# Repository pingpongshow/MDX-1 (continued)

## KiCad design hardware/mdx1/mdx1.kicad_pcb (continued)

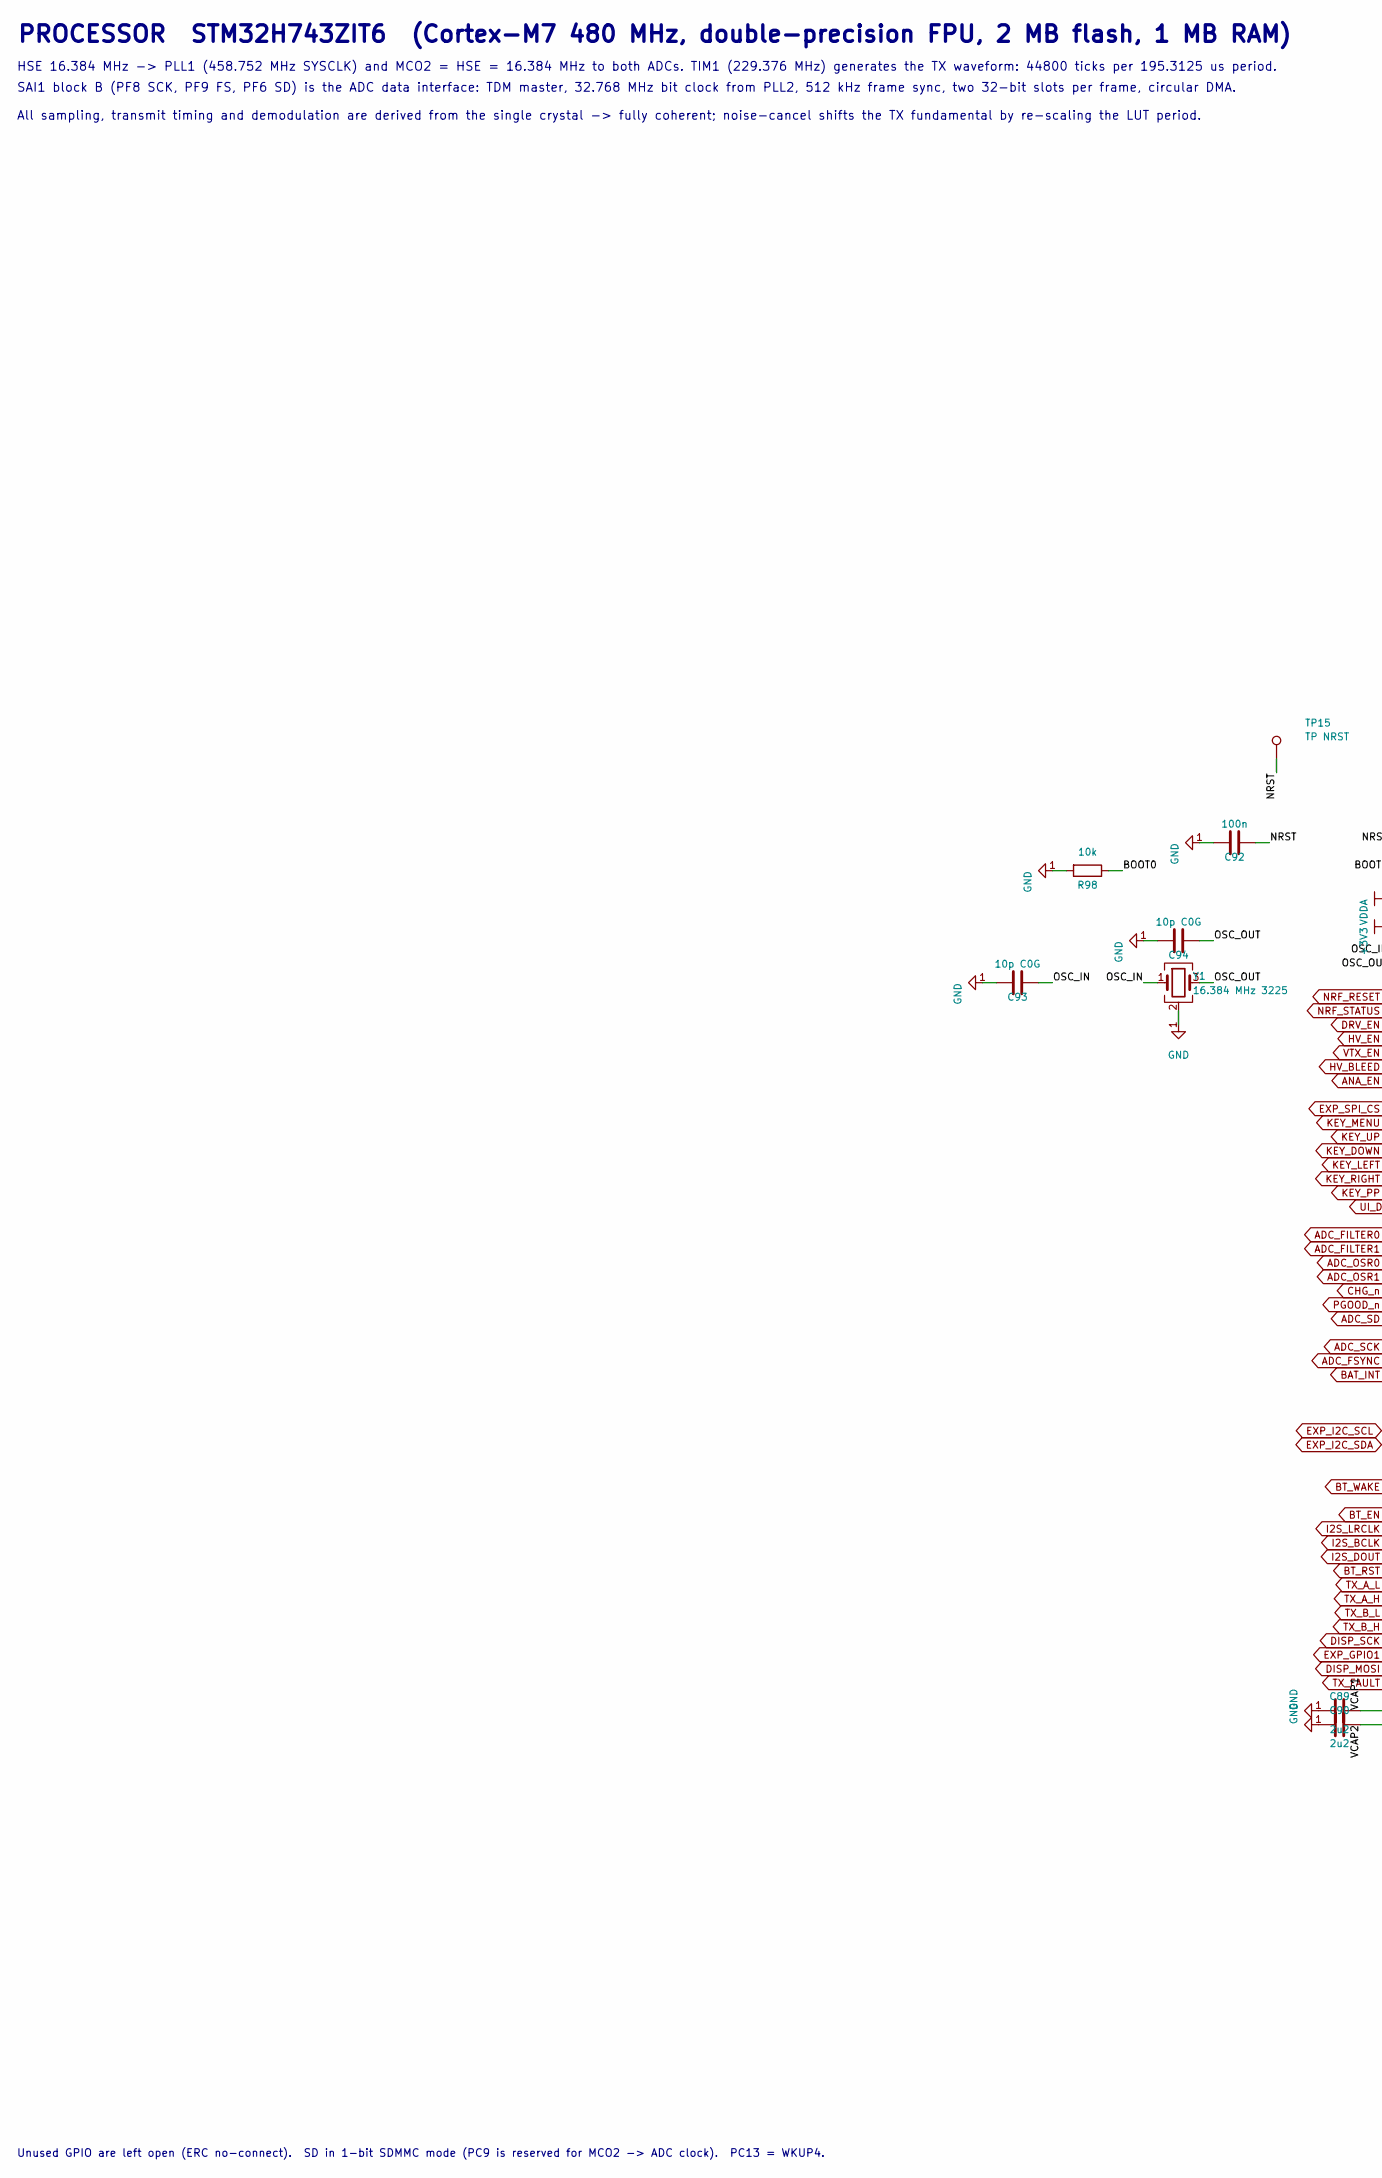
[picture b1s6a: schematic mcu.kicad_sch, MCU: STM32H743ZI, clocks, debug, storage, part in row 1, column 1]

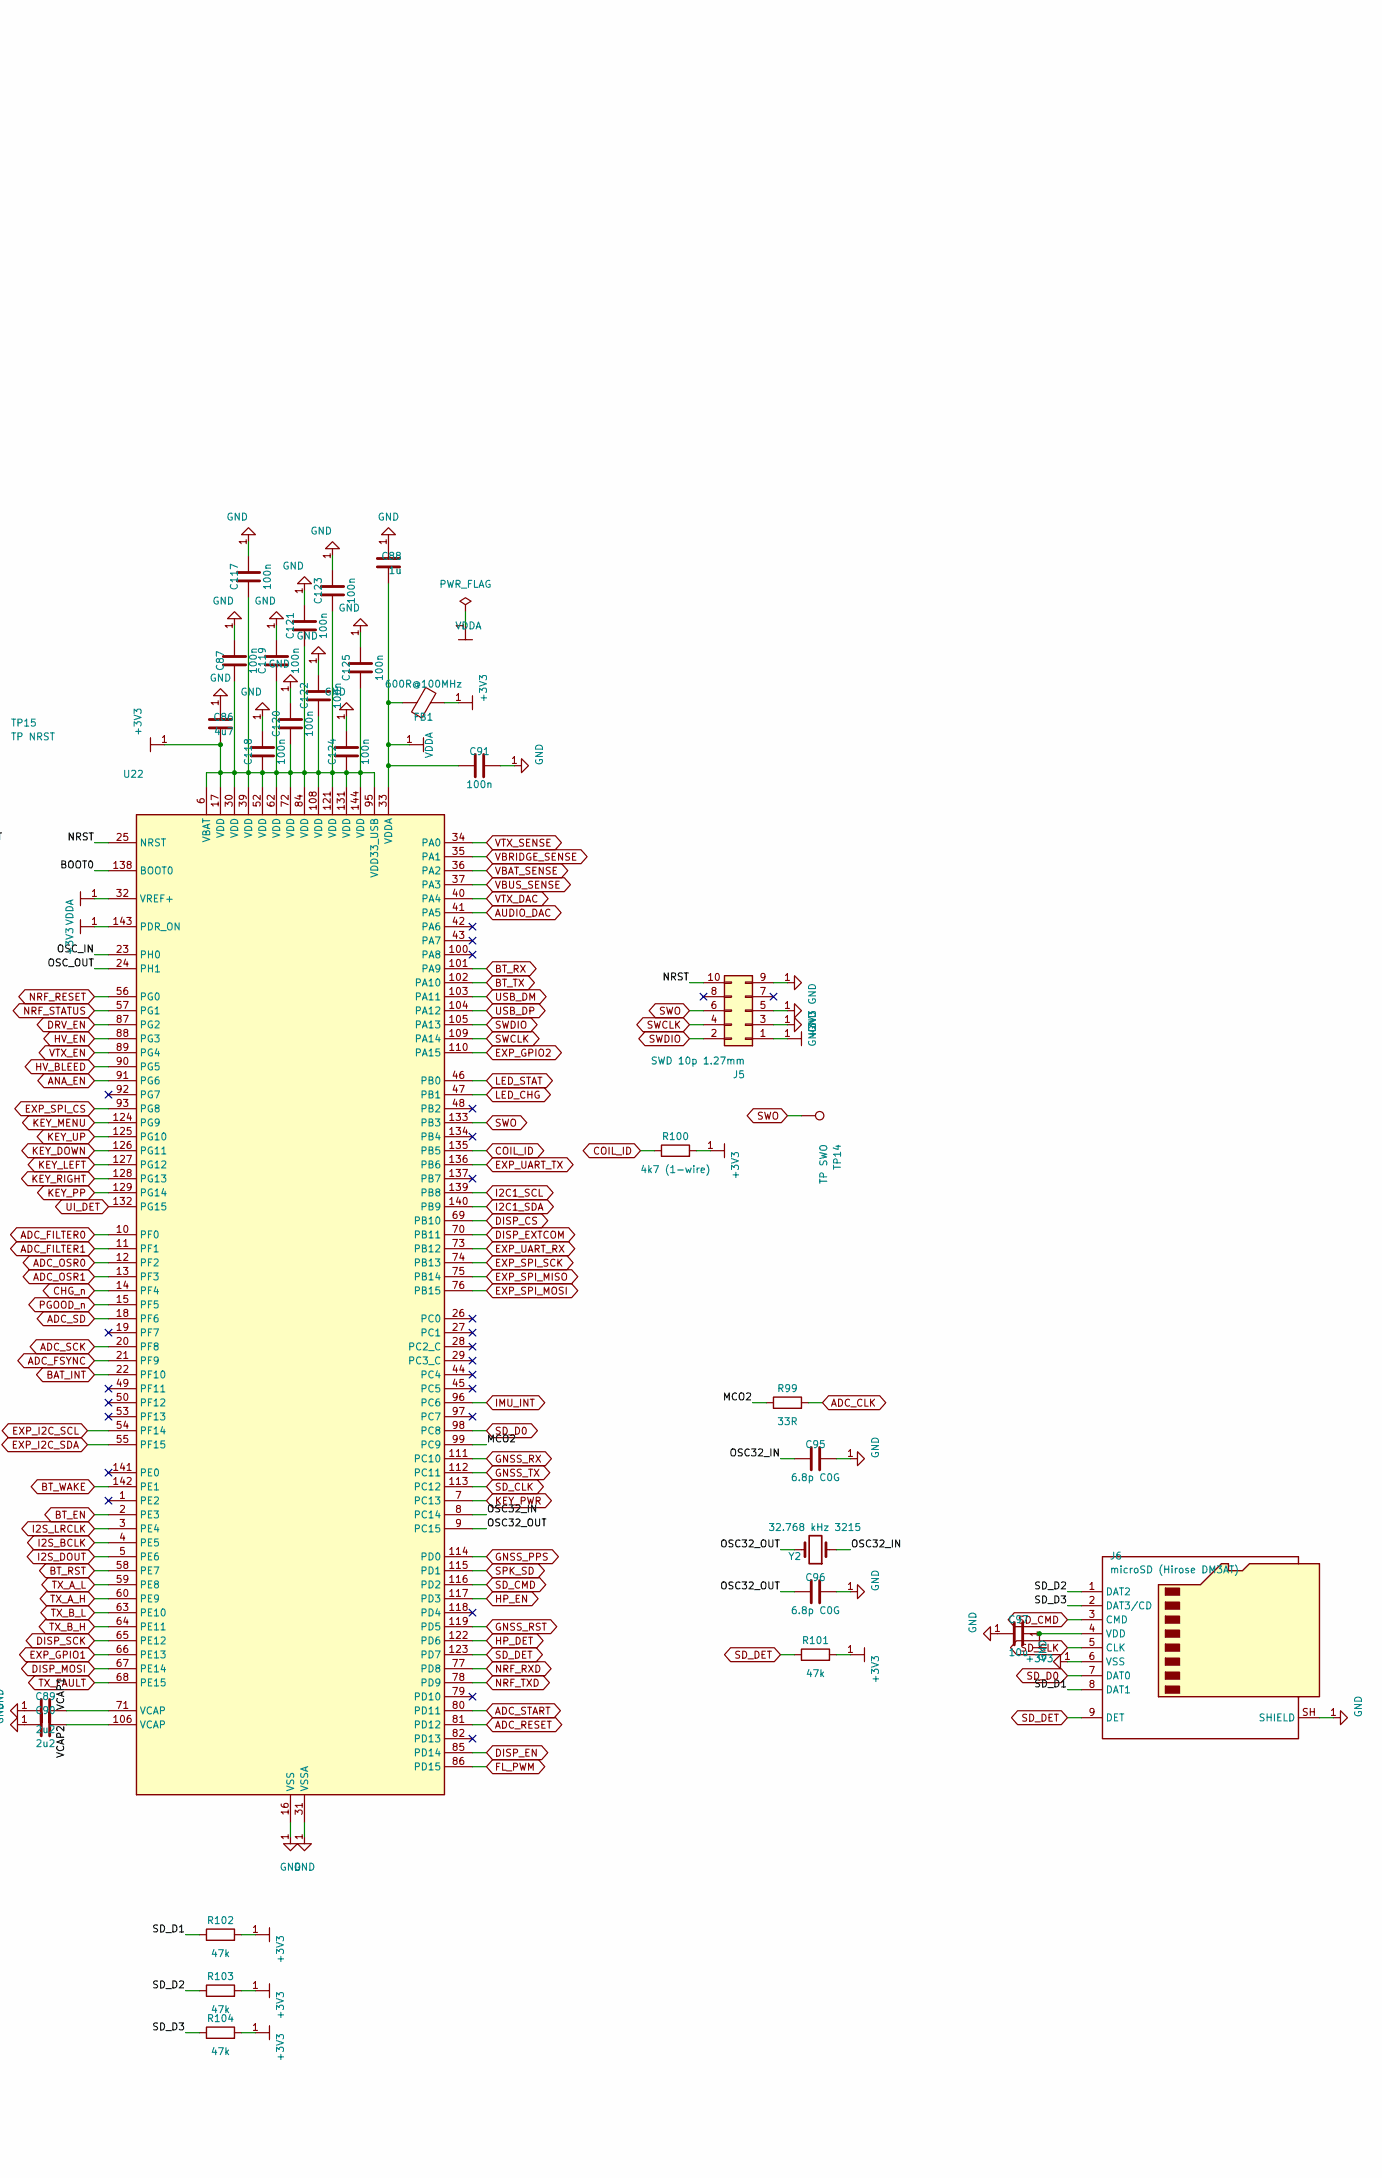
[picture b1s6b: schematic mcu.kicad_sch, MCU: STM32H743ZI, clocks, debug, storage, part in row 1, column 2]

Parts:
C86: 4u7; C_0603_1608Metric
C87, C91, C92, C117, C118, C119, C120, C121, C122, C123, C124, C125: 100n; C_0402_1005Metric
C88: 1u; C_0603_1608Metric
C89, C90: 2u2; C_0603_1608Metric
C93, C94: 10p C0G; C_0402_1005Metric
C95, C96: 6.8p C0G; C_0402_1005Metric
C97: 10u; C_0805_2012Metric
FB1: 600R@100MHz; L_0603_1608Metric
J5: SWD 10p 1.27mm; PinHeader_2x05_P1.27mm_Vertical
J6: microSD (Hirose DM3AT); microSD_HC_Hirose_DM3AT-SF-PEJM5
R98: 10k; R_0402_1005Metric
R99: 33R; R_0402_1005Metric
R100: 4k7 (1-wire); R_0402_1005Metric
R101, R102, R103, R104: 47k; R_0402_1005Metric
TP14: TP SWO; TestPoint_Pad_D1.5mm
TP15: TP NRST; TestPoint_Pad_D1.5mm
U22: STM32H743ZIT6; LQFP-144_20x20mm_P0.5mm
Y1: 16.384 MHz 3225; Crystal_SMD_3225-4Pin_3.2x2.5mm
Y2: 32.768 kHz 3215; Crystal_SMD_3215-2Pin_3.2x1.5mm

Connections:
+3V3: C86.1, C87.1, C97.1, C117.1, C118.1, C119.1, C120.1, C121.1, C122.1, C123.1, C124.1, C125.1, FB1.1, J5.1, J6.4 (VDD), R100.2, R101.2, R102.2, R103.2, R104.2, U22.6 (VBAT), U22.17 (VDD), U22.30 (VDD), U22.39 (VDD), U22.52 (VDD), U22.62 (VDD), U22.72 (VDD), U22.84 (VDD), U22.95 (VDD33_USB), U22.108 (VDD), U22.121 (VDD), U22.131 (VDD), U22.143 (PDR_ON), U22.144 (VDD); also elsewhere on the board
/MCU: STM32H743ZI, clocks, debug, storage/BOOT0: R98.1, U22.138 (BOOT0)
/MCU: STM32H743ZI, clocks, debug, storage/MCO2: R99.1, U22.99 (PC9)
/MCU: STM32H743ZI, clocks, debug, storage/NRST: C92.1, J5.10, TP15.1 (1_1), U22.25 (NRST)
/MCU: STM32H743ZI, clocks, debug, storage/OSC32_IN: C95.1, U22.8 (PC14), Y2.1
/MCU: STM32H743ZI, clocks, debug, storage/OSC32_OUT: C96.1, U22.9 (PC15), Y2.2
/MCU: STM32H743ZI, clocks, debug, storage/OSC_IN: C93.1, U22.23 (PH0), Y1.1
/MCU: STM32H743ZI, clocks, debug, storage/OSC_OUT: C94.1, U22.24 (PH1), Y1.3
/MCU: STM32H743ZI, clocks, debug, storage/SD_D1: J6.8 (DAT1), R102.1
/MCU: STM32H743ZI, clocks, debug, storage/SD_D2: J6.1 (DAT2), R103.1
/MCU: STM32H743ZI, clocks, debug, storage/SD_D3: J6.2 (DAT3/CD), R104.1
/MCU: STM32H743ZI, clocks, debug, storage/VCAP1: C89.1, U22.71 (VCAP)
/MCU: STM32H743ZI, clocks, debug, storage/VCAP2: C90.1, U22.106 (VCAP)
ADC_CLK: R99.2; also elsewhere on the board
ADC_FILTER0: U22.10 (PF0); also elsewhere on the board
ADC_FILTER1: U22.11 (PF1); also elsewhere on the board
ADC_FSYNC: U22.21 (PF9); also elsewhere on the board
ADC_OSR0: U22.12 (PF2); also elsewhere on the board
ADC_OSR1: U22.13 (PF3); also elsewhere on the board
ADC_RESET: U22.81 (PD12); also elsewhere on the board
ADC_SCK: U22.20 (PF8); also elsewhere on the board
ADC_SD: U22.18 (PF6); also elsewhere on the board
ADC_START: U22.80 (PD11); also elsewhere on the board
ANA_EN: U22.91 (PG6); also elsewhere on the board
AUDIO_DAC: U22.41 (PA5); also elsewhere on the board
BAT_INT: U22.22 (PF10); also elsewhere on the board
BT_EN: U22.2 (PE3); also elsewhere on the board
BT_RST: U22.58 (PE7); also elsewhere on the board
BT_RX: U22.101 (PA9); also elsewhere on the board
BT_TX: U22.102 (PA10); also elsewhere on the board
BT_WAKE: U22.142 (PE1); also elsewhere on the board
CHG_n: U22.14 (PF4); also elsewhere on the board
COIL_ID: R100.1, U22.135 (PB5); also elsewhere on the board
DISP_CS: U22.69 (PB10); also elsewhere on the board
DISP_EN: U22.85 (PD14); also elsewhere on the board
DISP_EXTCOM: U22.70 (PB11); also elsewhere on the board
DISP_MOSI: U22.67 (PE14); also elsewhere on the board
DISP_SCK: U22.65 (PE12); also elsewhere on the board
DRV_EN: U22.87 (PG2); also elsewhere on the board
EXP_GPIO1: U22.66 (PE13); also elsewhere on the board
EXP_GPIO2: U22.110 (PA15); also elsewhere on the board
EXP_I2C_SCL: U22.54 (PF14); also elsewhere on the board
EXP_I2C_SDA: U22.55 (PF15); also elsewhere on the board
EXP_SPI_CS: U22.93 (PG8); also elsewhere on the board
EXP_SPI_MISO: U22.75 (PB14); also elsewhere on the board
EXP_SPI_MOSI: U22.76 (PB15); also elsewhere on the board
EXP_SPI_SCK: U22.74 (PB13); also elsewhere on the board
EXP_UART_RX: U22.73 (PB12); also elsewhere on the board
EXP_UART_TX: U22.136 (PB6); also elsewhere on the board
FL_PWM: U22.86 (PD15); also elsewhere on the board
GNSS_PPS: U22.114 (PD0); also elsewhere on the board
GNSS_RST: U22.119 (PD5); also elsewhere on the board
GNSS_RX: U22.111 (PC10); also elsewhere on the board
GNSS_TX: U22.112 (PC11); also elsewhere on the board
HP_DET: U22.122 (PD6); also elsewhere on the board
HP_EN: U22.117 (PD3); also elsewhere on the board
HV_BLEED: U22.90 (PG5); also elsewhere on the board
HV_EN: U22.88 (PG3); also elsewhere on the board
I2C1_SCL: U22.139 (PB8); also elsewhere on the board
I2C1_SDA: U22.140 (PB9); also elsewhere on the board
I2S_BCLK: U22.4 (PE5); also elsewhere on the board
I2S_DOUT: U22.5 (PE6); also elsewhere on the board
I2S_LRCLK: U22.3 (PE4); also elsewhere on the board
IMU_INT: U22.96 (PC6); also elsewhere on the board
KEY_DOWN: U22.126 (PG11); also elsewhere on the board
KEY_LEFT: U22.127 (PG12); also elsewhere on the board
KEY_MENU: U22.124 (PG9); also elsewhere on the board
KEY_PP: U22.129 (PG14); also elsewhere on the board
KEY_PWR: U22.7 (PC13); also elsewhere on the board
KEY_RIGHT: U22.128 (PG13); also elsewhere on the board
KEY_UP: U22.125 (PG10); also elsewhere on the board
LED_CHG: U22.47 (PB1); also elsewhere on the board
LED_STAT: U22.46 (PB0); also elsewhere on the board
NRF_RESET: U22.56 (PG0); also elsewhere on the board
NRF_RXD: U22.77 (PD8); also elsewhere on the board
NRF_STATUS: U22.57 (PG1); also elsewhere on the board
NRF_TXD: U22.78 (PD9); also elsewhere on the board
PGOOD_n: U22.15 (PF5); also elsewhere on the board
SD_CLK: J6.5 (CLK), U22.113 (PC12)
SD_CMD: J6.3 (CMD), U22.116 (PD2)
SD_D0: J6.7 (DAT0), U22.98 (PC8)
SD_DET: J6.9 (DET), R101.1, U22.123 (PD7)
SPK_SD: U22.115 (PD1); also elsewhere on the board
SWCLK: J5.4, U22.109 (PA14)
SWDIO: J5.2, U22.105 (PA13)
SWO: J5.6, TP14.1 (1_1), U22.133 (PB3)
TX_A_H: U22.60 (PE9); also elsewhere on the board
TX_A_L: U22.59 (PE8); also elsewhere on the board
TX_B_H: U22.64 (PE11); also elsewhere on the board
TX_B_L: U22.63 (PE10); also elsewhere on the board
TX_FAULT: U22.68 (PE15); also elsewhere on the board
UI_DET: U22.132 (PG15); also elsewhere on the board
USB_DM: U22.103 (PA11); also elsewhere on the board
USB_DP: U22.104 (PA12); also elsewhere on the board
VBAT_SENSE: U22.36 (PA2); also elsewhere on the board
VBRIDGE_SENSE: U22.35 (PA1); also elsewhere on the board
VBUS_SENSE: U22.37 (PA3); also elsewhere on the board
VDDA: C88.1, C91.1, FB1.2, U22.32 (VREF+), U22.33 (VDDA)
VTX_DAC: U22.40 (PA4); also elsewhere on the board
VTX_EN: U22.89 (PG4); also elsewhere on the board
VTX_SENSE: U22.34 (PA0); also elsewhere on the board

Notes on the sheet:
SAI1 block B (PF8 SCK, PF9 FS, PF6 SD) is the ADC data interface: TDM master, 32.768 MHz bit clock from PLL2, 512 kHz frame sync, two 32-bit slots per frame, circular DMA.
All sampling, transmit timing and demodulation are derived from the single crystal -> fully coherent; noise-cancel shifts the TX fundamental by re-scaling the LUT period.
HSE 16.384 MHz -> PLL1 (458.752 MHz SYSCLK) and MCO2 = HSE = 16.384 MHz to both ADCs. TIM1 (229.376 MHz) generates the TX waveform: 44800 ticks per 195.3125 us period.
Unused GPIO are left open (ERC no-connect). SD in 1-bit SDMMC mode (PC9 is reserved for MCO2 -> ADC clock). PC13 = WKUP4.
PROCESSOR STM32H743ZIT6 (Cortex-M7 480 MHz, double-precision FPU, 2 MB flash, 1 MB RAM)

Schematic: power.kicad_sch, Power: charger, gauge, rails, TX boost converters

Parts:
C1, C27: 4u7 10V; C_0603_1608Metric
C2, C3, C6, C9, C26: 10u 10V; C_0805_2012Metric
C4, C10, C28: 100n; C_0402_1005Metric
C5, C24, C25: 1u; C_0603_1608Metric
C7, C8: 22u 6.3V; C_0805_2012Metric
C11, C34: 220n; C_0402_1005Metric
C12: 10n (CP); C_0402_1005Metric
C13: 4n7 (CN); C_0402_1005Metric
C14, C15, C16: 22u 25V; C_1210_3225Metric
C17: 1u 25V; C_0603_1608Metric
C18, C21: 4u7 25V; C_0805_2012Metric
C19, C22: 10u 25V; C_0805_2012Metric
C20, C23, C29, C35: 4u7; C_0603_1608Metric
C30: 4n7; C_0402_1005Metric
C31: 100u 50V; CP_Radial_D8.0mm_P3.50mm
C32: 10u 50V; C_1210_3225Metric
C33: 4u7 50V; C_1210_3225Metric
C36: 10n; C_0402_1005Metric
C37: 47u 160V; CP_Radial_D10.0mm_P5.00mm
C38, C39: 2u2 250V; C_2220_5750Metric
D1: SMAJ5.0A TVS; D_SMA
D2, D3: SS34; D_SMA
D4: B560C 60V 5A; D_SMC
D5: STPS2150 150V; D_SMA
J1: USB-C 16P; USB_C_Receptacle_HRO_TYPE-C-31-M-12
J2: USBLC6-2SC6 (USB ESD); SOT-23-6
J3: Battery JST-PH 3p; JST_PH_B3B-PH-K_1x03_P2.00mm_Vertical
L1: 1u5 XAL4020; L_Coilcraft_XAL4020-XXX
L2, L3: 4u7 XAL4020; L_Coilcraft_XAL4020-XXX
L4: 22u XAL7050; L_Coilcraft_XAL7050-XXX
L5: 47u XAL7050; L_Coilcraft_XAL7050-XXX
Q1: SiR680ADP-T1-UE3; PowerPAK_SO-8_Single
Q2: BSC190N15NS3 (150V); Infineon_PG-TDSON-8_6.15x5.15mm
Q3: BSS127S (600V); SOT-23
R1, R2: 5k1; R_0402_1005Metric
R3: 1k1 (IIN 1.4A); R_0402_1005Metric
R4: 887R (ICHG 1A); R_0402_1005Metric
R5: 47k (timer); R_0402_1005Metric
R6: 10k (TS, DNP w/ NTC); R_0402_1005Metric
R7, R8, R14, R15, R24, R46: 100k; R_0402_1005Metric
R9: 10m 1% (gauge); R_1206_3216Metric
R10, R11, R16, R19, R37: 10k; R_0402_1005Metric
R12, R13: 4k7; R_0402_1005Metric
R17, R36: 47k; R_0402_1005Metric
R18, R29, R39: 22k; R_0402_1005Metric
R20: 100R (VIN filter); R_0402_1005Metric
R21: 1M; R_0402_1005Metric
R22: 113k; R_0402_1005Metric
R23: 499k; R_0402_1005Metric
R25, R26: 49k9 0.1% SET (100uA); R_0402_1005Metric
R27: 10R (LCD supply); R_0402_1005Metric
R28: 41k2 (300kHz); R_0402_1005Metric
R30, R35: 442k; R_0402_1005Metric
R31: 40k2; R_0402_1005Metric
R32: 66k5; R_0402_1005Metric
R33: 20m (sense); R_1206_3216Metric
R34, R44: 10R; R_0402_1005Metric
R38: 140k (100kHz); R_0402_1005Metric
R40, R41: 619k; R_0402_1005Metric
R42: 20k0; R_0402_1005Metric
R43: 50m (sense); R_1206_3216Metric
R45: 10k 1W (bleed); R_2512_6332Metric
U1: BQ24075RGT; VQFN-16-1EP_3x3mm_P0.5mm_EP1.6x1.6mm
U2: BQ27441DRZT-G1A; Texas_S-PDSO-N12
U3: TPS63001 (3.3V); Texas_DRC0010J_ThermalVias
U4: TPS65131RGET; Texas_RGE0024H_VQFN-24-1EP_4x4mm_P0.5mm_EP2.7x2.7mm_Thermal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
U5: LT3045 (+5VA); MSOP-12-1EP_3x4.039mm_P0.65mm_EP1.651x2.845mm
U6: LT3094 (-5VA); MSOP-12-1EP_3x4.039mm_P0.65mm_EP1.651x2.845mm
U7: TPS7A2033 (+3V3A); SOT-23-5
U8: LT3757 (VTX 8-30V); MSOP-10-1EP_3x3mm_P0.5mm_EP1.68x1.88mm
U9: LT3757 (VBRIDGE 100V); MSOP-10-1EP_3x3mm_P0.5mm_EP1.68x1.88mm

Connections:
+3V3: C7.1, C8.1, R7.2, R8.2, R12.2, R13.2, U3.1 (VOUT), U3.10 (FB); also elsewhere on the board
+3V3A: C25.1, U7.5 (OUT); also elsewhere on the board
+5VA: C19.1, C24.1, R27.1, U5.10 (OUTS), U5.11 (OUT), U5.12 (OUT), U7.1 (IN), U7.3 (EN); also elsewhere on the board
+5V_LCD: C26.1, R27.2; also elsewhere on the board
+12V: C14.1, C15.1, C18.1, D2.1 (K), R21.1, U4.23 (VPOS), U5.1 (IN), U5.2 (IN), U5.3 (IN), U5.4 (EN/UV), U5.7 (PGFB); also elsewhere on the board
-5VA: C22.1, U6.10 (OUTS), U6.11 (OUT), U6.12 (OUT); also elsewhere on the board
-6V: C16.1, C17.1, C21.1, D3.2 (A), R23.2, U4.15 (VNEG), U6.1 (IN), U6.2 (IN), U6.3 (EN/UV), U6.5 (PGFB), U6.13 (IN)
/Power: charger, gauge, rails, TX boost converters/BAT_PACK+: C4.1, J3.1, R9.1, U2.6 (BAT), U2.8 (SRP)
/Power: charger, gauge, rails, TX boost converters/BAT_TS: J3.2, R6.1, U1.1 (TS)
/Power: charger, gauge, rails, TX boost converters/CC1: J1.A5 (CC1), R1.1
/Power: charger, gauge, rails, TX boost converters/CC2: J1.B5 (CC2), R2.1
/Power: charger, gauge, rails, TX boost converters/CHG_ILIM: R3.1, U1.12 (ILIM)
/Power: charger, gauge, rails, TX boost converters/CHG_ISET: R4.1, U1.16 (ISET)
/Power: charger, gauge, rails, TX boost converters/CHG_TMR: R5.1, U1.14 (TMR)
/Power: charger, gauge, rails, TX boost converters/CN_COMP: C13.1, U4.18 (CN)
/Power: charger, gauge, rails, TX boost converters/CP_COMP: C12.1, U4.21 (CP)
/Power: charger, gauge, rails, TX boost converters/FBN: R23.1, R24.1, U4.16 (FBN)
/Power: charger, gauge, rails, TX boost converters/FBP: R21.2, R22.1, U4.22 (FBP)
/Power: charger, gauge, rails, TX boost converters/GAUGE_BIN: R10.1, U2.10 (BIN)
/Power: charger, gauge, rails, TX boost converters/HV_BLEED_D: Q3.2 (D), R45.2
/Power: charger, gauge, rails, TX boost converters/HV_CS: Q2.3 (S), R43.1, U9.6 (SENSE)
/Power: charger, gauge, rails, TX boost converters/HV_FB: R41.2, R42.1, U9.2 (FBX)
/Power: charger, gauge, rails, TX boost converters/HV_FB_M: R40.2, R41.1
/Power: charger, gauge, rails, TX boost converters/HV_GATE: Q2.1 (G), R44.2
/Power: charger, gauge, rails, TX boost converters/HV_GATE_R: R44.1, U9.7 (GATE)
/Power: charger, gauge, rails, TX boost converters/HV_INTVCC: C35.1, U9.8 (INTVCC)
/Power: charger, gauge, rails, TX boost converters/HV_RT: R38.1, U9.4 (RT)
/Power: charger, gauge, rails, TX boost converters/HV_SS: C34.1, U9.3 (SS)
/Power: charger, gauge, rails, TX boost converters/HV_VC: R39.1, U9.1 (VC)
/Power: charger, gauge, rails, TX boost converters/HV_VC_C: C36.1, R39.2
/Power: charger, gauge, rails, TX boost converters/SET_5VA: C20.1, R25.1, U5.8 (SET)
/Power: charger, gauge, rails, TX boost converters/SET_N5VA: C23.1, R26.1, U6.8 (SET)
/Power: charger, gauge, rails, TX boost converters/SW3V3_A: L1.1, U3.4 (L1)
/Power: charger, gauge, rails, TX boost converters/SW3V3_B: L1.2, U3.2 (L2)
/Power: charger, gauge, rails, TX boost converters/SW_HV: D5.2 (A), L5.2, Q2.2 (D)
/Power: charger, gauge, rails, TX boost converters/SW_NEG: D3.1 (K), L3.1, U4.13 (OUTN), U4.14 (OUTN)
/Power: charger, gauge, rails, TX boost converters/SW_POS: D2.2 (A), L2.2, U4.1 (INP), U4.24 (INP)
/Power: charger, gauge, rails, TX boost converters/SW_VTX: D4.2 (A), L4.2, Q1.2 (D)
/Power: charger, gauge, rails, TX boost converters/USB_DM_C: J1.A7 (D-), J1.B7 (D-), J2.3 (I/O2)
/Power: charger, gauge, rails, TX boost converters/USB_DP_C: J1.A6 (D+), J1.B6 (D+), J2.1 (I/O1)
/Power: charger, gauge, rails, TX boost converters/VBAT_DIV: R14.2, R15.1, R16.1
/Power: charger, gauge, rails, TX boost converters/VBUS_DIV: R17.2, R18.1, R19.1
/Power: charger, gauge, rails, TX boost converters/VIN_65131: C10.1, R20.2, U4.4 (VIN)
/Power: charger, gauge, rails, TX boost converters/VREF_65131: C11.1, R24.2, U4.17 (VREF)
/Power: charger, gauge, rails, TX boost converters/VTX_CS: Q1.3 (S), R33.1, U8.6 (SENSE)
/Power: charger, gauge, rails, TX boost converters/VTX_DIV: R35.2, R36.1, R37.1
/Power: charger, gauge, rails, TX boost converters/VTX_FB: R30.2, R31.1, R32.1, U8.2 (FBX)
/Power: charger, gauge, rails, TX boost converters/VTX_GATE: Q1.1 (G), R34.2
/Power: charger, gauge, rails, TX boost converters/VTX_GATE_R: R34.1, U8.7 (GATE)
/Power: charger, gauge, rails, TX boost converters/VTX_INTVCC: C29.1, U8.8 (INTVCC)
/Power: charger, gauge, rails, TX boost converters/VTX_RT: R28.1, U8.4 (RT)
/Power: charger, gauge, rails, TX boost converters/VTX_SS: C28.1, U8.3 (SS)
/Power: charger, gauge, rails, TX boost converters/VTX_VC: R29.1, U8.1 (VC)
ANA_EN: U4.8 (ENP), U4.10 (ENN); also elsewhere on the board
BAT_INT: R11.1, U2.12 (GPOUT); also elsewhere on the board
CHG_n: R8.1, U1.9 (~CHG); also elsewhere on the board
GAUGE_VDD: C5.1, R11.2, U2.5 (V_{DD})
HV_BLEED: Q3.1 (G), R46.1; also elsewhere on the board
HV_EN: U9.9 (~SHDN/UVLO); also elsewhere on the board
I2C1_SCL: R13.1, U2.2 (SCL); also elsewhere on the board
I2C1_SDA: R12.1, U2.1 (SDA); also elsewhere on the board
PGOOD_n: R7.1, U1.7 (~PGOOD); also elsewhere on the board
USB_DM: J2.4 (I/O2); also elsewhere on the board
USB_DP: J2.6 (I/O1); also elsewhere on the board
VBAT: C3.1, R9.2, R14.1, U1.2 (BAT), U1.3 (BAT), U2.7 (SRN); also elsewhere on the board
VBAT_SENSE: R16.2; also elsewhere on the board
VBRIDGE: C37.1, C38.1, C39.1, D5.1 (K), R40.1, R45.1; also elsewhere on the board
VBUS: C1.1, D1.1 (A1), J1.A4 (VBUS), J1.A9 (VBUS), J1.B4 (VBUS), J1.B9 (VBUS), J2.5 (VBUS), R17.1, U1.5 (EN2), U1.13 (IN)
VBUS_SENSE: R19.2; also elsewhere on the board
VSYS: C2.1, C6.1, C9.1, C27.1, L2.1, L4.1, R20.1, U1.10 (OUT), U1.11 (OUT), U3.5 (VIN), U3.6 (EN), U3.7 (PS/SYNC), U3.8 (VINA), U4.5 (INN), U4.6 (INN), U8.10 (VIN); also elsewhere on the board
VTX: C31.1, C32.1, C33.1, D4.1 (K), L5.1, R30.1, R35.1, U9.10 (VIN)
VTX_DAC: R32.2; also elsewhere on the board
VTX_EN: U8.9 (~SHDN/UVLO); also elsewhere on the board
VTX_SENSE: R37.2; also elsewhere on the board

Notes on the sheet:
MDX-1 POWER TREE
1S Li-ion 21700 (5 Ah) -> BQ24075 power-path charger (USB-C 5 V) -> VSYS. VSYS -> TPS63001 buck-boost +3V3 (digital);
VTX = 1.6V*(1+442k/40.2k+442k/66.5k) - VDAC*(442k/66.5k) -> 29.8 V @ 0 V DAC, 7.9 V @ 3.3 V DAC. VBRIDGE = 1.6V*(1+1.238M/20k) = 100.6 V.
Capacitors drawn at a pin belong to that pin (PCB placement follows the schematic).
LT3757 #1: VSYS -> VTX programmable 8..30 V (DAC-steered feedback) = VLF transmit rail. LT3757 #2: VTX -> VBRIDGE 100 V for PI/ZVT mode (off in VLF: VBRIDGE = VTX - Vf).
+5V_LCD: the memory LCD is a 5 V panel (VDD 4.8-5.5 V, VIH 2.7 V min, so 3.3 V logic is fine); 10R/10u keeps its refresh current off the analog rail.
HV_BLEED: MCU discharges the 100 V bank (27 uF, 0.13 J) through 10k (1 W pulse rated) in ~1.4 s when leaving PI mode.
TPS65131 -> +12V (gate drivers, feeds LT3045 +5VA ultra-low-noise LDO) and -6V (feeds LT3094 -5VA LDO); TPS7A20 -> +3V3A (ADC/ref).

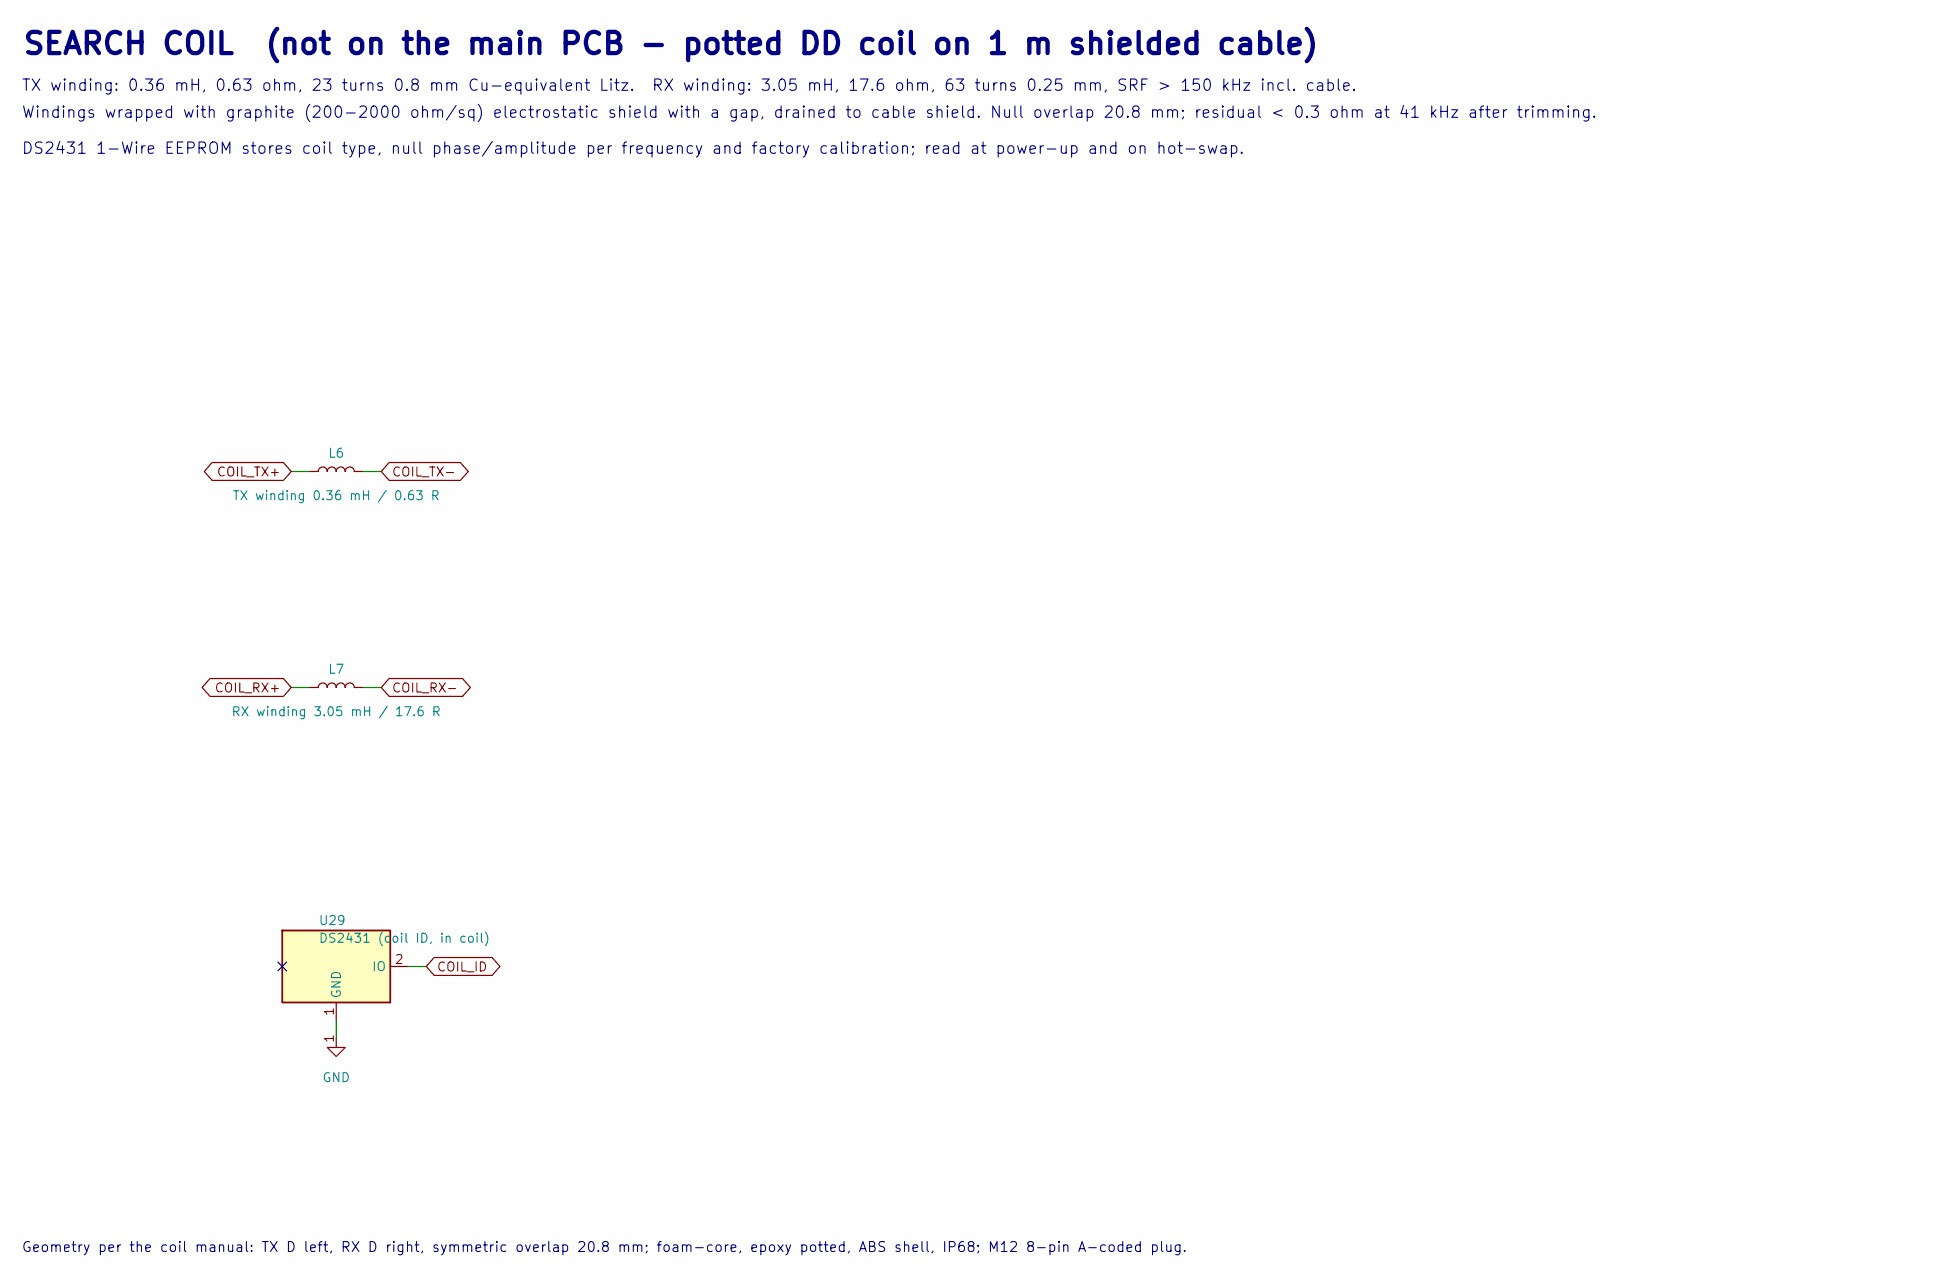
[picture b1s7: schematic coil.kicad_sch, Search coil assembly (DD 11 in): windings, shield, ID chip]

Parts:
L6: TX winding 0.36 mH / 0.63 R
L7: RX winding 3.05 mH / 17.6 R
U29: DS2431 (coil ID, in coil); SOT-23

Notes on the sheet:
Windings wrapped with graphite (200-2000 ohm/sq) electrostatic shield with a gap, drained to cable shield. Null overlap 20.8 mm; residual < 0.3 ohm at 41 kHz after trimming.
TX winding: 0.36 mH, 0.63 ohm, 23 turns 0.8 mm Cu-equivalent Litz. RX winding: 3.05 mH, 17.6 ohm, 63 turns 0.25 mm, SRF > 150 kHz incl. cable.
Geometry per the coil manual: TX D left, RX D right, symmetric overlap 20.8 mm; foam-core, epoxy potted, ABS shell, IP68; M12 8-pin A-coded plug.
SEARCH COIL (not on the main PCB - potted DD coil on 1 m shielded cable)
DS2431 1-Wire EEPROM stores coil type, null phase/amplitude per frequency and factory calibration; read at power-up and on hot-swap.
